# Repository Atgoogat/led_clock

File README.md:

# LED Clock

This is the pcb and software for a clock showing the time as three vertical led bars. 

The hours are split in two bars, 13h to 23h and 1h-12h, while minutes are split in three groups of 15, 5 and single minutes. Summed up you can read the time.

Time is kept with an RTC-DS3231.
Because the outputs of the arduino uno are not sufficient, shift registers are used to output the time.

Result:

## Questions

Please contact me via github if you have any questions or want to rebuild this clock 😉.

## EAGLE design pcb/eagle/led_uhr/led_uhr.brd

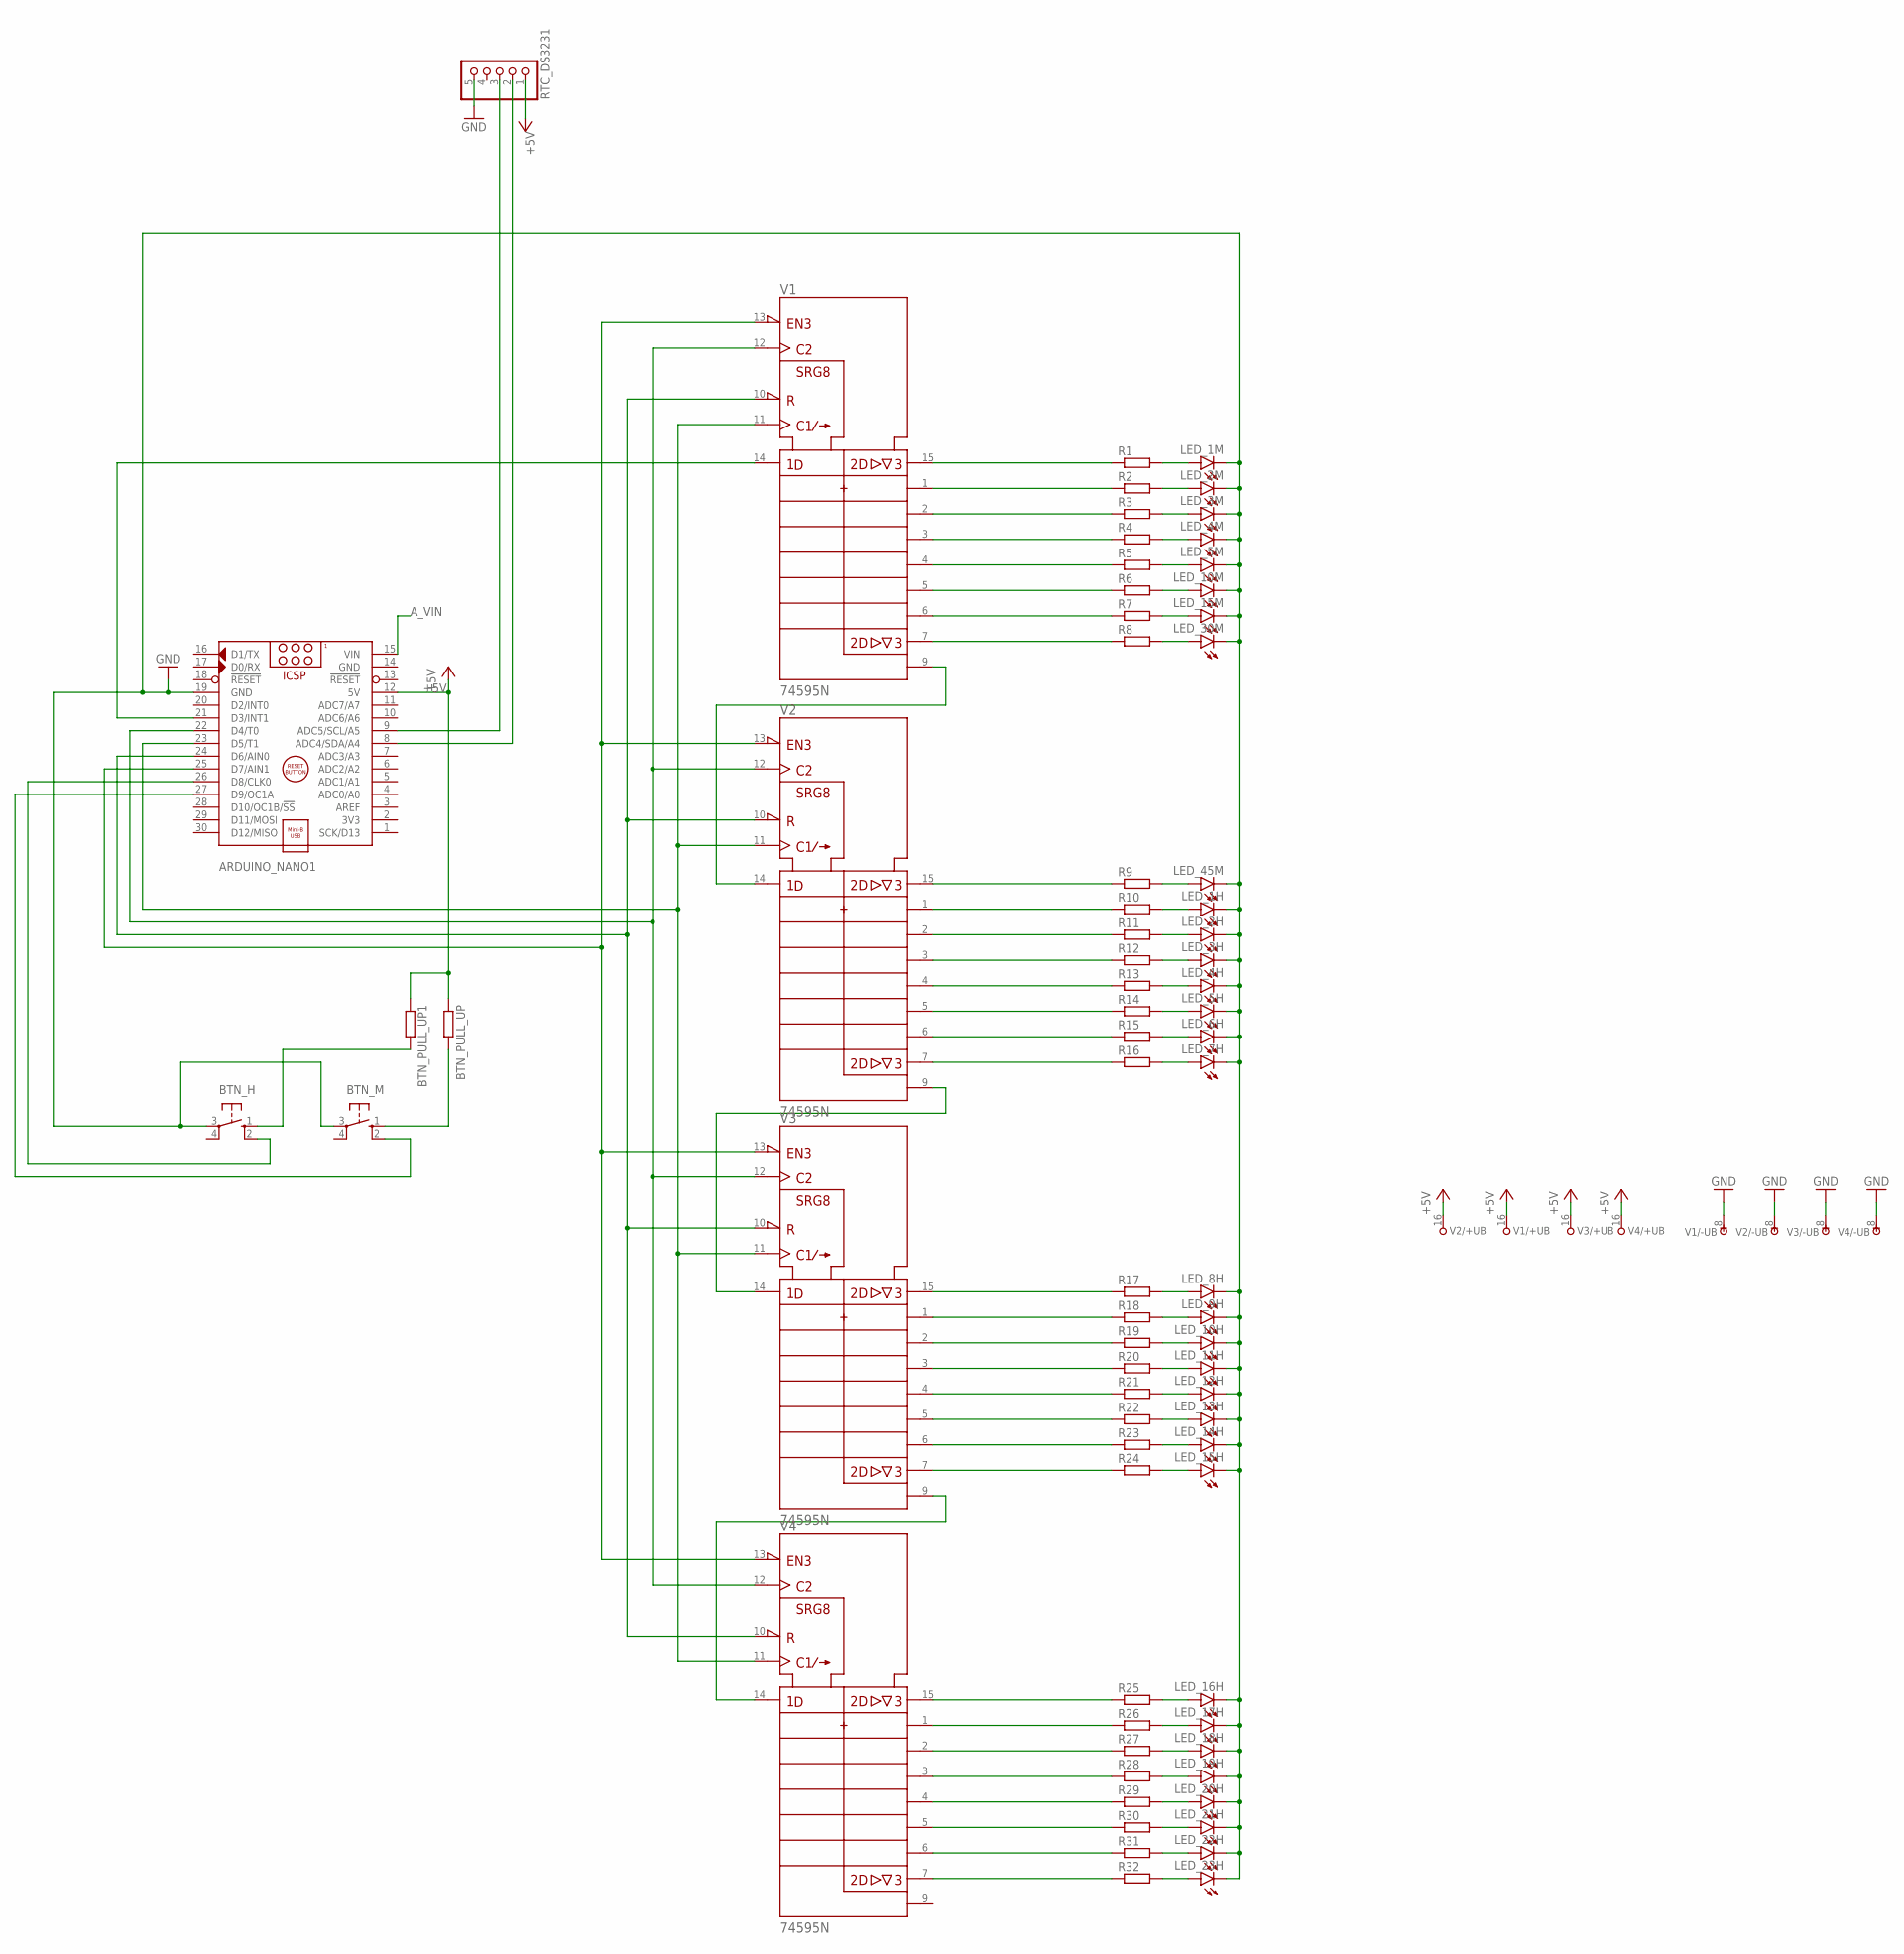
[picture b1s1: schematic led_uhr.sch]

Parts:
ARDUINO_NANO1: ARDUINO_NANO
BTN_H: 40-XX; B3F-40XX
BTN_M: 40-XX; B3F-40XX
BTN_PULL_UP, BTN_PULL_UP1: R-EU_0207/10; 0207/10
LED_1H, LED_1M, LED_2H, LED_2M, LED_3H, LED_3M, LED_4H, LED_4M, LED_5H, LED_5M, LED_6H, LED_7H, LED_8H, LED_9H, LED_10H, LED_10M, LED_11H, LED_12H, LED_13H, LED_14H, LED_15H, LED_15M, LED_16H, LED_17H, LED_18H, LED_19H, LED_20H, LED_21H, LED_22H, LED_23H, LED_30M, LED_45M: LED5MM
R1, R2, R3, R4, R5, R6, R7, R8, R9, R10, R11, R12, R13, R14, R15, R16, R17, R18, R19, R20, R21, R22, R23, R24, R25, R26, R27, R28, R29, R30, R31, R32: R-EU_0207/10; 0207/10
RTC_DS3231: PINHD-1X5; 1X05
V1, V2, V3, V4: 74595N; DIL16

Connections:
+5V: ARDUINO_NANO1.12 (5V), BTN_PULL_UP.1, BTN_PULL_UP1.1, RTC_DS3231.1, V1.16 (+UB), V2.16 (+UB), V3.16 (+UB), V4.16 (+UB)
A_VIN: ARDUINO_NANO1.15 (VIN)
GND: ARDUINO_NANO1.14 (GND), ARDUINO_NANO1.19 (GND), BTN_H.3, BTN_M.3, LED_1H.K (C), LED_1M.K (C), LED_2H.K (C), LED_2M.K (C), LED_3H.K (C), LED_3M.K (C), LED_4H.K (C), LED_4M.K (C), LED_5H.K (C), LED_5M.K (C), LED_6H.K (C), LED_7H.K (C), LED_8H.K (C), LED_9H.K (C), LED_10H.K (C), LED_10M.K (C), LED_11H.K (C), LED_12H.K (C), LED_13H.K (C), LED_14H.K (C), LED_15H.K (C), LED_15M.K (C), LED_16H.K (C), LED_17H.K (C), LED_18H.K (C), LED_19H.K (C), LED_20H.K (C), LED_21H.K (C), LED_22H.K (C), LED_23H.K (C), LED_30M.K (C), LED_45M.K (C), RTC_DS3231.5, V1.8 (-UB), V2.8 (-UB), V3.8 (-UB), V4.8 (-UB)
unnamed: R1.1, V1.15 (QA)
unnamed: R2.1, V1.1 (QB)
unnamed: R3.1, V1.2 (QC)
unnamed: R4.1, V1.3 (QD)
unnamed: R5.1, V1.4 (QE)
unnamed: R6.1, V1.5 (QF)
unnamed: R7.1, V1.6 (QG)
unnamed: R8.1, V1.7 (QH)
unnamed: R10.1, V2.1 (QB)
unnamed: R9.1, V2.15 (QA)
unnamed: R11.1, V2.2 (QC)
unnamed: R12.1, V2.3 (QD)
unnamed: R13.1, V2.4 (QE)
unnamed: R14.1, V2.5 (QF)
unnamed: R15.1, V2.6 (QG)
unnamed: R16.1, V2.7 (QH)
unnamed: R17.1, V3.15 (QA)
unnamed: R18.1, V3.1 (QB)
unnamed: R19.1, V3.2 (QC)
unnamed: R20.1, V3.3 (QD)
unnamed: R21.1, V3.4 (QE)
unnamed: R22.1, V3.5 (QF)
unnamed: R23.1, V3.6 (QG)
unnamed: R24.1, V3.7 (QH)
unnamed: R25.1, V4.15 (QA)
unnamed: R26.1, V4.1 (QB)
unnamed: R27.1, V4.2 (QC)
unnamed: R28.1, V4.3 (QD)
unnamed: R29.1, V4.4 (QE)
unnamed: R30.1, V4.5 (QF)
unnamed: R31.1, V4.6 (QG)
unnamed: R32.1, V4.7 (QH)
unnamed: V1.9 (QH*), V2.14 (SER)
unnamed: V2.9 (QH*), V3.14 (SER)
unnamed: V3.9 (QH*), V4.14 (SER)
unnamed: LED_1M.A, R1.2
unnamed: LED_2M.A, R2.2
unnamed: LED_3M.A, R3.2
unnamed: LED_4M.A, R4.2
unnamed: LED_5M.A, R5.2
unnamed: LED_10M.A, R6.2
unnamed: LED_15M.A, R7.2
unnamed: LED_30M.A, R8.2
unnamed: LED_45M.A, R9.2
unnamed: LED_1H.A, R10.2
unnamed: LED_2H.A, R11.2
unnamed: LED_3H.A, R12.2
unnamed: LED_4H.A, R13.2
unnamed: LED_5H.A, R14.2
unnamed: LED_6H.A, R15.2
unnamed: LED_7H.A, R16.2
unnamed: LED_8H.A, R17.2
unnamed: LED_9H.A, R18.2
unnamed: LED_10H.A, R19.2
unnamed: LED_11H.A, R20.2
unnamed: LED_12H.A, R21.2
unnamed: LED_13H.A, R22.2
unnamed: LED_14H.A, R23.2
unnamed: LED_15H.A, R24.2
unnamed: LED_16H.A, R25.2
unnamed: LED_17H.A, R26.2
unnamed: LED_18H.A, R27.2
unnamed: LED_19H.A, R28.2
unnamed: LED_20H.A, R29.2
unnamed: LED_21H.A, R30.2
unnamed: LED_22H.A, R31.2
unnamed: LED_23H.A, R32.2
unnamed: ARDUINO_NANO1.23 (D5/T1), V1.11 (SRCK), V2.11 (SRCK), V3.11 (SRCK), V4.11 (SRCK)
unnamed: ARDUINO_NANO1.24 (D6/AIN0), V1.10 (!SRCLR), V2.10 (!SRCLR), V3.10 (!SRCLR), V4.10 (!SRCLR)
unnamed: ARDUINO_NANO1.21 (D3/INT1), V1.14 (SER)
unnamed: ARDUINO_NANO1.22 (D4/T0), V1.12 (RCK), V2.12 (RCK), V3.12 (RCK), V4.12 (RCK)
unnamed: ARDUINO_NANO1.25 (D7/AIN1), V1.13 (!G), V2.13 (!G), V3.13 (!G), V4.13 (!G)
unnamed: BTN_M.1 (S), BTN_PULL_UP.2
unnamed: ARDUINO_NANO1.27 (D9/OC1A), BTN_M.2 (S1)
unnamed: ARDUINO_NANO1.9 (ADC5/SCL/A5), RTC_DS3231.3
unnamed: ARDUINO_NANO1.8 (ADC4/SDA/A4), RTC_DS3231.2
unnamed: ARDUINO_NANO1.26 (D8/CLK0), BTN_H.2 (S1)
unnamed: BTN_H.1 (S), BTN_PULL_UP1.2

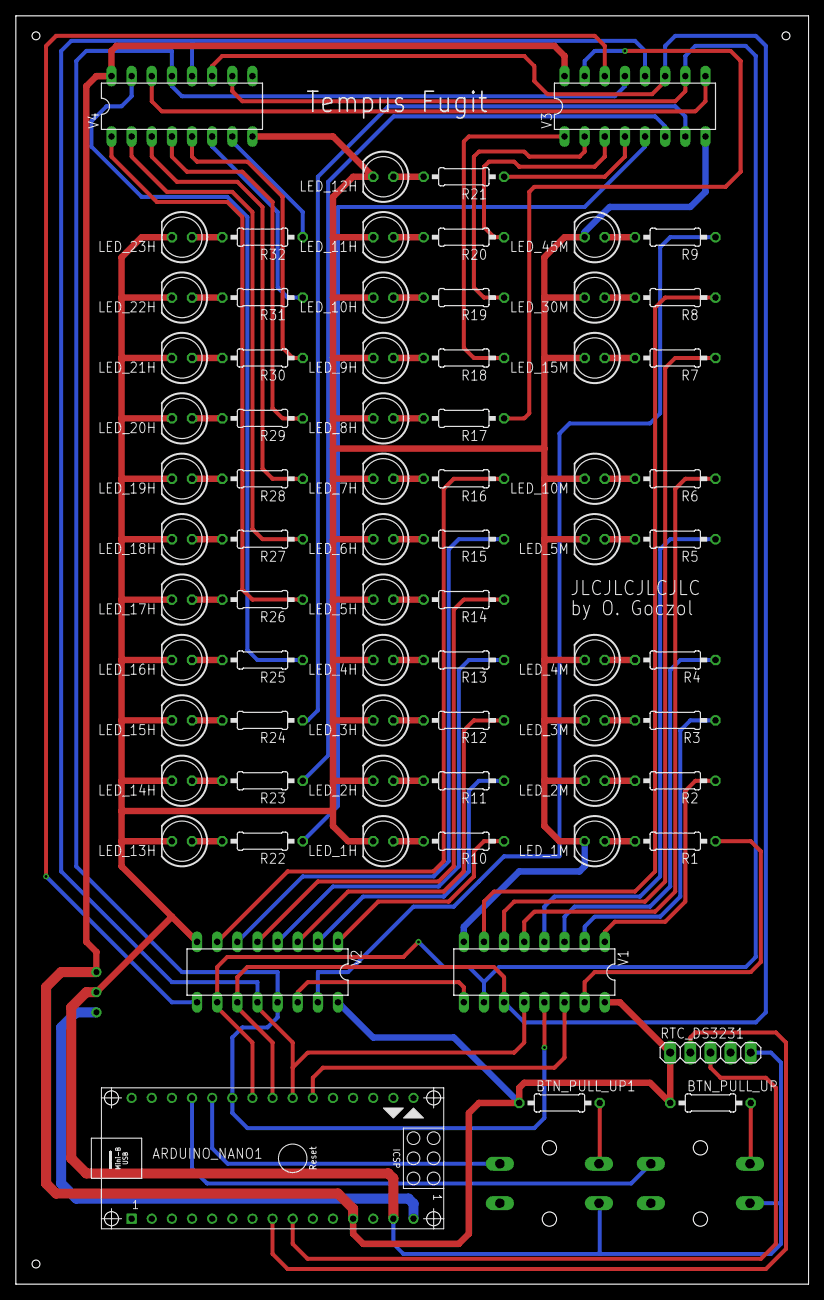
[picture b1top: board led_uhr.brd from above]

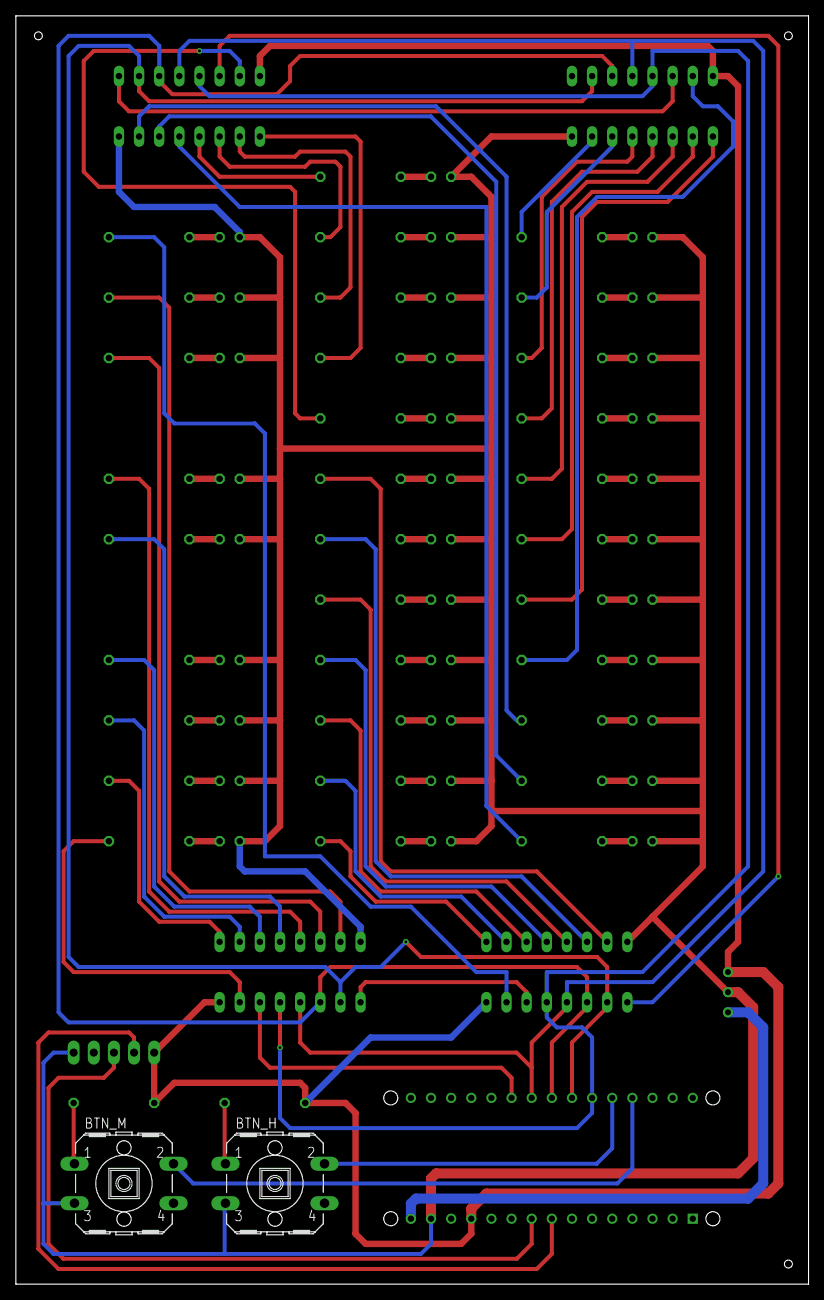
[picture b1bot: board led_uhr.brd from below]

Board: 2 copper layers, 100.0 x 160.0 mm, 74 parts (2 on the bottom side), 80 nets.

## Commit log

2022-07-21 fix: set time modulo precedence
2022-07-21 add: pcb files
2022-07-21 add: readme for github
